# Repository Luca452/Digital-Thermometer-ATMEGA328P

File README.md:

# Digital-Thermometer-ATMEGA328P
Simple digital thermometer based on LM335 sensor using an ATMEGA328P

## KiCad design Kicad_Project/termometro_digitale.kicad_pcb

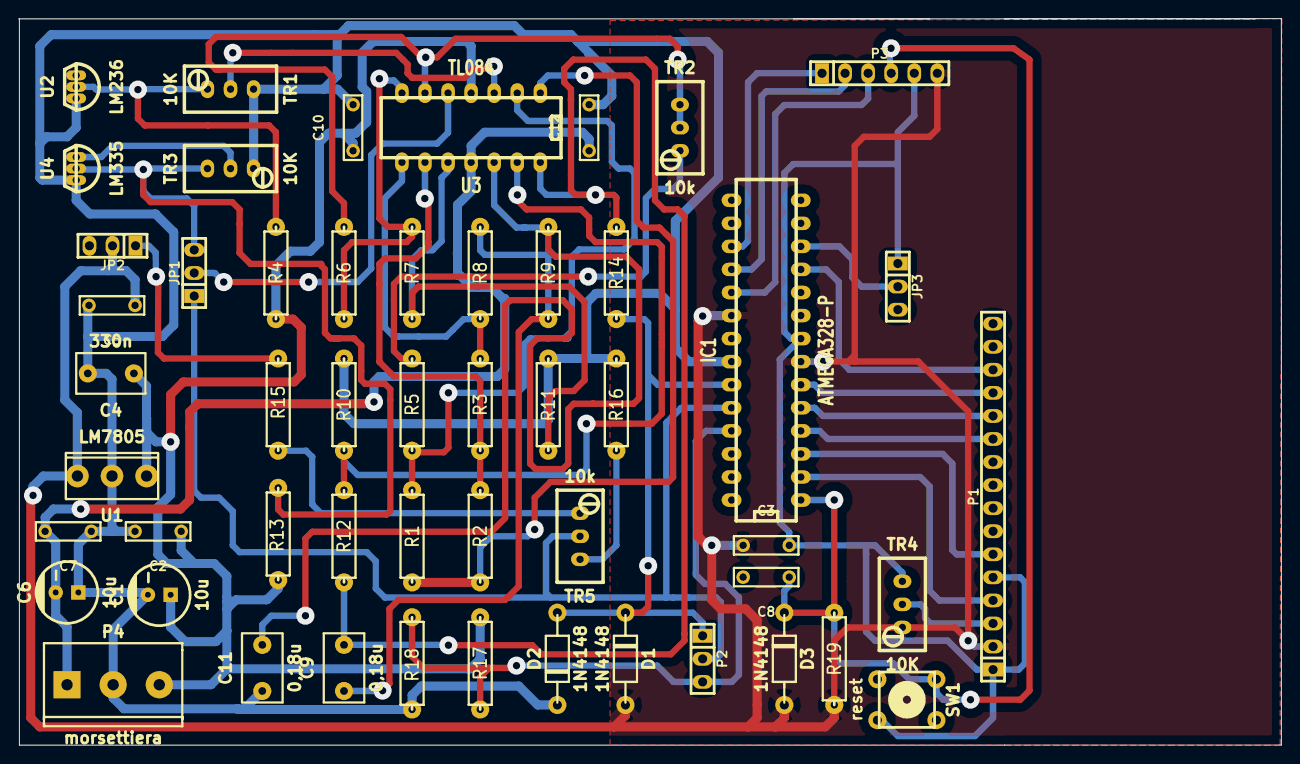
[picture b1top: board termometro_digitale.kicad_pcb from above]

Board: 2 copper layers, 139.1 x 80.0 mm, 52 parts (0 on the bottom side), 39 nets.

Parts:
C1, C6: 10u; CP_6.3x5mm
C2, C3, C5, C7, C8, C10, C12: 100n; cnp_7.5mm_disc
C4: 330n; cnp_7x4.5mm
C9, C11: 0,18u; cnp_7x4.5mm
D1, D2, D3: 1N4148; diode_do41
IC1: ATMEGA328-P; dil_28-300
JP1, JP2: TAR TERM; pin_strip_3
JP3: JUMPER3; pin_strip_3
P1: strip femmina; pin_strip_16
P2: test points; pin_socket_3
P3: strip femmina; pin_socket_6
P4: morsettiera; mors_3p
R1, R2, R3, R6, R7, R11: 15k; RC05
R4: 1,2k; RC05
R5, R14: 6,8k; RC05
R8, R9: 3,9M; RC05
R10: 56k; RC05
R12: 33k; RC05
R13, R15, R16: 2,2K; RC05
R17, R18: 1M; RC05
R19: 10k; RC05
SW1: reset; PCB_PUSH
TR1, TR3, TR4: 10K; trimmer_vishay_64w
TR2, TR5: 10k; trimmer_vishay_64w
U1: LM7805; to220
U2: LM236; to92_3_flat
U3: TL084; dil_14-300
U4: LM335; to92_3_flat

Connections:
+5V: C3.1, C5.1, D1.1, D3.1, IC1.7, IC1.20, JP2.2, P1.2, P3.6, R19.1, TR4.1, U1.3
+9V: C1.1, C2.1, C4.1, C10.1, P4.3, R4.2, R13.2, R17.1, U1.1, U3.4
-9V: C6.2, C7.2, C12.1, P4.1, U3.11
/ADC0: D1.2, D2.1, IC1.23, P2.1, R14.1
/ADC1: IC1.24, JP1.1, P2.2, TR5.2
/ADC2: IC1.25, P2.3, R17.2, R18.1
/LCD4: IC1.2, P1.4
/LCD6: IC1.3, P1.6
/LCD11: IC1.4, P1.11
/LCD12: IC1.5, P1.12
/LCD13: IC1.6, P1.13
/LCD14: IC1.11, P1.14
/MISO: IC1.18, P3.2
/MOSI: IC1.17, P3.1
/RESET: C8.1, D3.2, IC1.1, P3.4, R19.2, SW1.1
/SCK: IC1.19, P3.3
/v+: JP1.2, U3.5
GNDA: C1.2, C2.2, C3.2, C4.2, C5.2, C6.1, C7.1, C8.2, C10.2, C11.1, C12.2, D2.2, IC1.8, IC1.22, JP3.1, P1.1, P1.5, P3.5, P4.2, R10.2, R11.1, R16.1, R18.2, SW1.2, TR1.3, TR3.1, TR4.3, U1.2, U2.1, U4.1
unnamed: C9.1, R8.1, R9.2
unnamed: C9.2, R12.2, R14.2, U3.14
unnamed: C11.2, R9.1, U3.12
unnamed: IC1.12, JP3.2
unnamed: JP1.3, R13.1, TR3.3, U4.2
unnamed: JP2.1, R15.2
unnamed: P1.3, TR4.2
unnamed: R1.1, R5.1, U3.2
unnamed: R1.2, R2.1, U3.1
unnamed: R2.2, R3.1, U3.9
unnamed: R3.2, R8.2, U3.8
unnamed: R4.1, TR1.1, U2.2
unnamed: R5.2, TR2.1
unnamed: R6.1, TR2.2, TR2.3, U3.6
unnamed: R6.2, R7.1, U3.7
unnamed: R10.1, R12.1, U3.13
unnamed: R7.2, R11.2, U3.10
unnamed: R15.1, TR5.1
unnamed: R16.2, TR5.3
unnamed: TR1.2, U3.3
unnamed: TR3.2, U4.3

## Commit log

2024-02-06 Added Kicad Files
